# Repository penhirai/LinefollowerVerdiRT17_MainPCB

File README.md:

# LinefollowerVerdiRT17_MainPCB
Micromouse Robotrace Competition

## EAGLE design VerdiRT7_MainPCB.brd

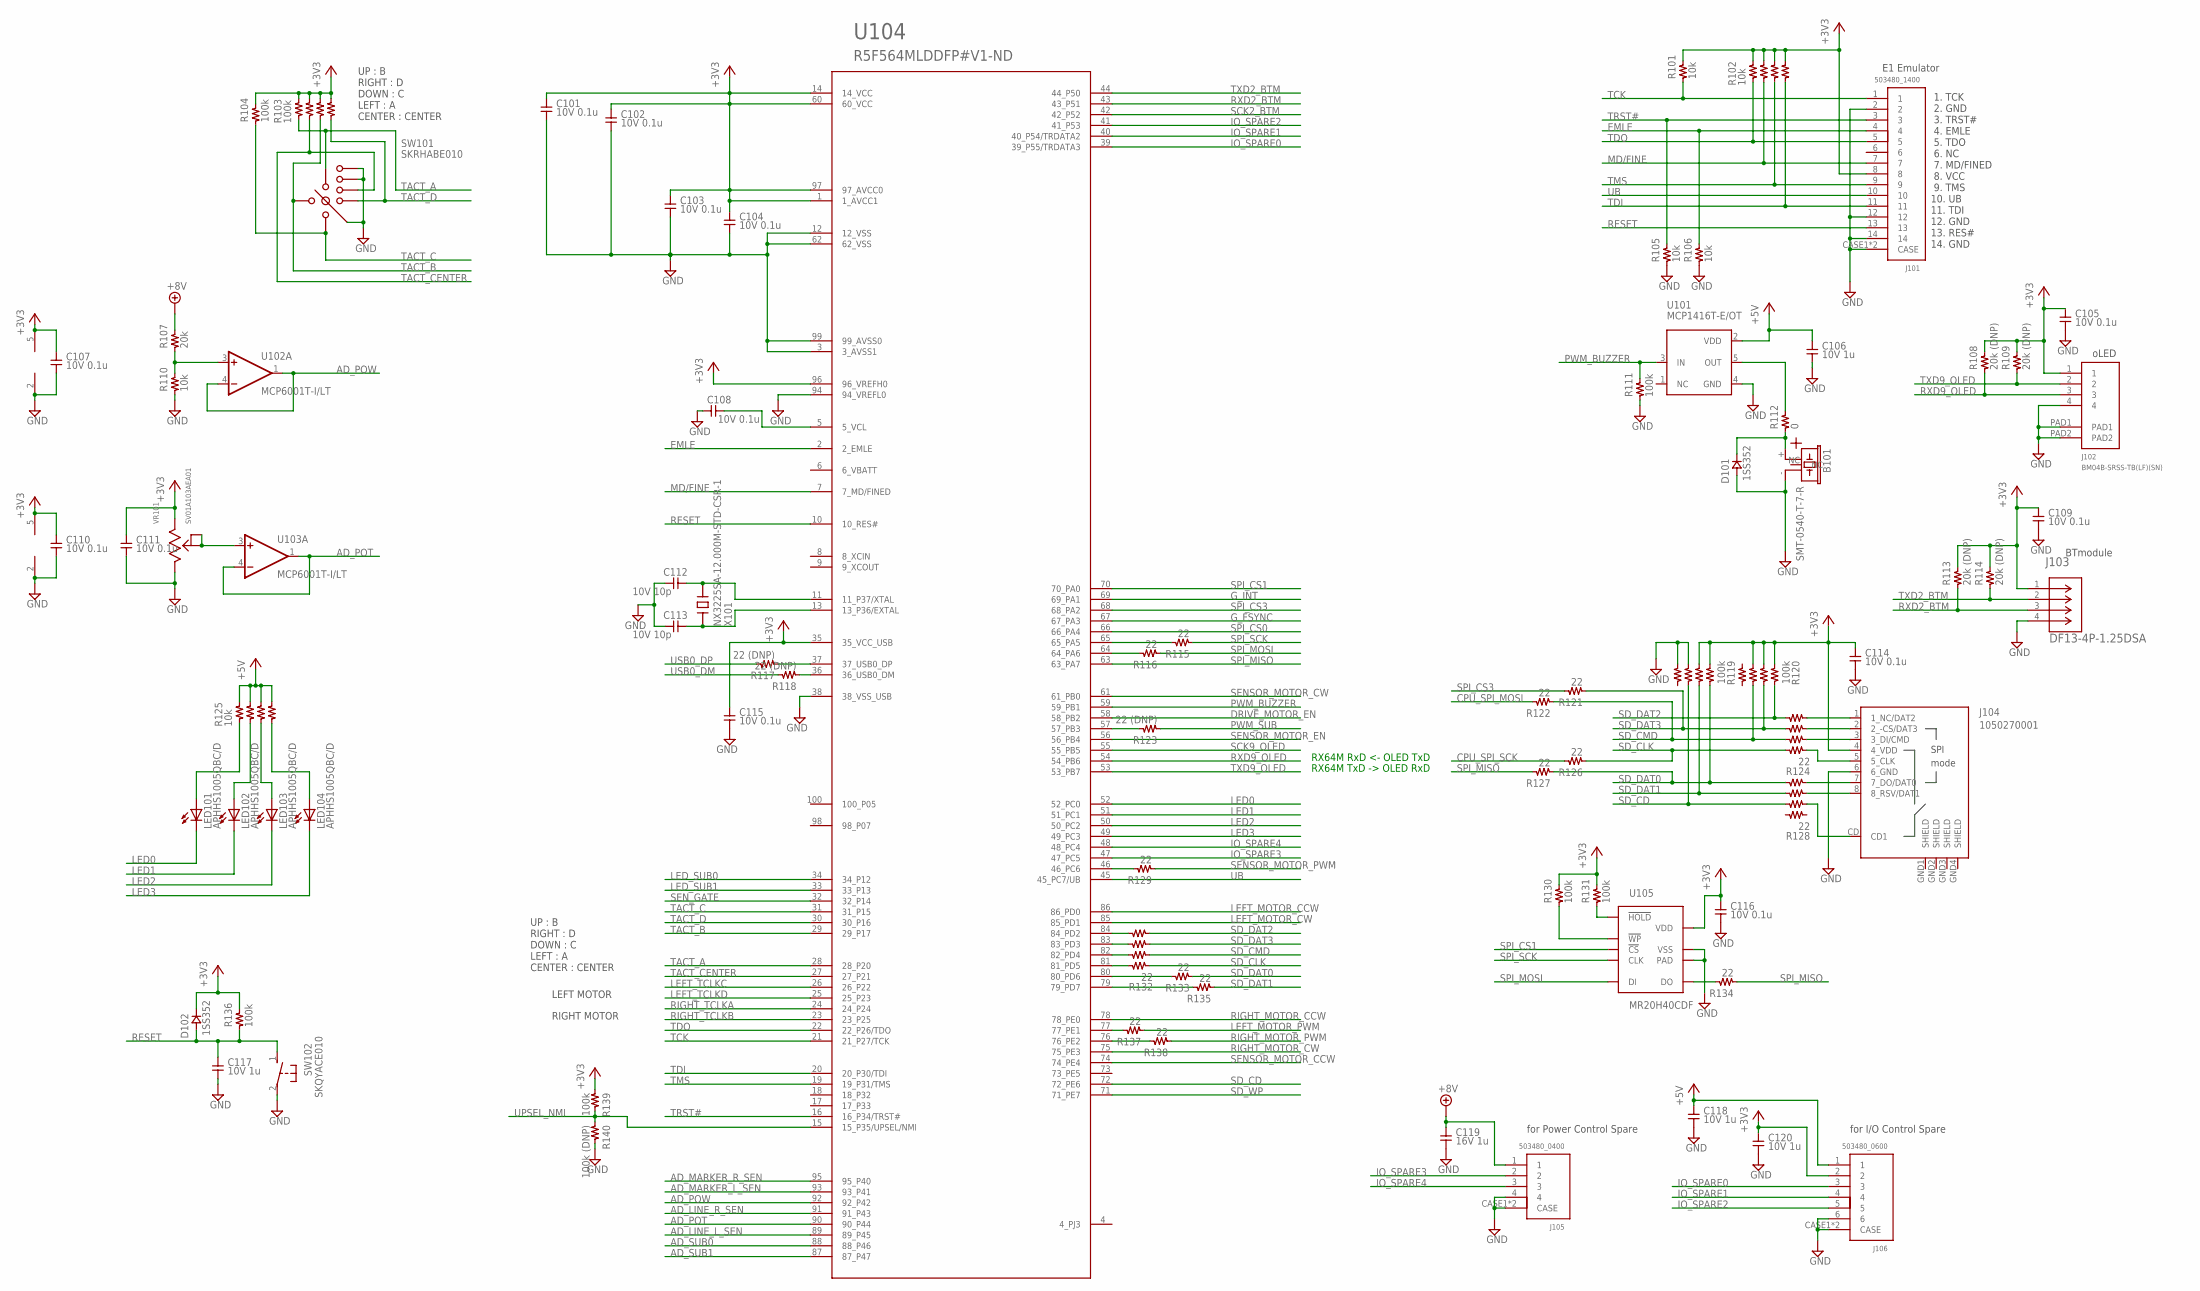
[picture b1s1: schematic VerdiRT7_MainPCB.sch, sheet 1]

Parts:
B101: SMT-0540-T-7-R; SMT-0540-S-R
C101, C102, C103, C104, C105, C107, C108, C109, C110, C111, C114, C115, C116: 10V 0.1u; 1005
C106, C117, C118, C120: 10V 1u; 1005
C112, C113: 10V 10p; 1005
C119: 16V 1u; 1005
D101, D102: 1SS352; 2012
J101: 503480_1400; 1400
J102: BM04B-SRSS-TB(LF)(SN); BM04B-SRSS-TB
J103: DF13-4P-1.25DSA; DF13_4P_TH
J104: 1050270001; MOLEX_105027
J105: 503480_0400; 0400
J106: 503480_0600; 0600
LED101, LED102, LED103, LED104: APHHS1005QBC/D; 1005
R101, R105, R106, R110: 10k; 1005
R102, R125: 10k; 3216_ARRAY
R103, R119, R120: 100k; 3216_ARRAY
R104, R111, R130, R131, R136, R139: 100k; 1005
R107: 20k; 1005
R108, R109, R113, R114: 20k (DNP); 1005
R112: 0; 1005
R115, R116, R121, R122, R126, R127, R129, R133, R134, R135, R137, R138: 22; 1005
R117, R118, R123: 22 (DNP); 1005
R124, R128, R132: 22; 3216_ARRAY
R140: 100k (DNP); 1005
SW101: SKRHABE010; SKRH
SW102: SKQYACE010; SKQYA
U101: MCP1416T-E/OT; SOT23-5
U102, U103: MCP6001T-I/LT; SOT-70-5
U104: R5F564MLDDFP#V1-ND; TQFP100-16X16
U105: MR20H40CDF; 8DFN
VR101: SV01A103AEA01; SV01
X101: NX3225SA-12.000M-STD-CSR-1; 3225

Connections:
+3V3: C101.P$1, C102.P$1, C103.P$1, C104.P$1, C105.P$1, C107.P$1, C109.P$1, C110.P$1, C111.P$1, C114.P$1, C115.P$1, C116.P$1, C120.P$1, D102.K, J101.8, J102.1, J103.1, J104.4 (4_VDD), J106.2, R101.P$2, R102.R1-B, R102.R2-B, R102.R3-B, R102.R4-B, R103.R1-B, R103.R2-B, R103.R3-B, R103.R4-B, R104.P$2, R108.P$2, R109.P$2, R113.P$2, R114.P$2, R119.R1-A, R119.R2-A, R120.R1-A, R120.R2-A, R120.R3-A, R130.P$2, R131.P$2, R136.P$2, R139.P$1, U102.5 (V+), U103.5 (V+), U104.1 (1_AVCC1), U104.14 (14_VCC), U104.35 (35_VCC_USB), U104.60 (60_VCC), U104.96 (96_VREFH0), U104.97 (97_AVCC0), U105.8 (VDD), VR101.2; also elsewhere on the board
+5V: C106.P$1, C118.P$1, J106.1, R125.R1-B, R125.R2-B, R125.R3-B, R125.R4-B, U101.2 (VDD); also elsewhere on the board
+8V: C119.P$1, J105.1, R107.P$2; also elsewhere on the board
AD_LINE_L_SEN: U104.89 (89_P45); also elsewhere on the board
AD_LINE_R_SEN: U104.91 (91_P43); also elsewhere on the board
AD_MARKER_L_SEN: U104.93 (93_P41); also elsewhere on the board
AD_MARKER_R_SEN: U104.95 (95_P40); also elsewhere on the board
AD_POT: U103.1 (OUT), U103.4 (-IN), U104.90 (90_P44)
AD_POW: U102.1 (OUT), U102.4 (-IN), U104.92 (92_P42)
AD_SUB0: U104.88 (88_P46)
AD_SUB1: U104.87 (87_P47)
CPU_SD_DAT0: R133.P$2, U104.80 (80_PD6)
CPU_SPI_MOSI: R116.P$2, R122.P$2, U104.64 (64_PA6)
CPU_SPI_SCK: R115.P$2, R126.P$2, U104.65 (65_PA5)
DRIVE_MOTOR_EN: U104.58 (58_PB2); also elsewhere on the board
EMLE: J101.4, R106.P$2, U104.2 (2_EMLE)
GND: B101.-, C101.P$2, C102.P$2, C103.P$2, C104.P$2, C105.P$2, C106.P$2, C107.P$2, C108.P$2, C109.P$2, C110.P$2, C111.P$2, C112.P$2, C113.P$2, C114.P$2, C115.P$2, C116.P$2, C117.P$2, C118.P$2, C119.P$2, C120.P$2, D101.A, J101.2, J101.12, J101.14, J101.CASE1 (CASE), J101.CASE2 (CASE), J102.4, J102.PAD1, J102.PAD2, J103.4, J104.6 (6_GND), J105.4, J105.CASE1 (CASE), J105.CASE2 (CASE), J106.6, J106.CASE1 (CASE), J106.CASE2 (CASE), R105.P$1, R106.P$1, R110.P$1, R111.P$1, R119.R3-A, R119.R4-A, R140.P$2, SW101.1, SW101.2, SW101.COMMON, SW102.2, U101.4 (GND), U102.2 (V-), U103.2 (V-), U104.3 (3_AVSS1), U104.12 (12_VSS), U104.38 (38_VSS_USB), U104.62 (62_VSS), U104.94 (94_VREFL0), U104.99 (99_AVSS0), U105.4 (VSS), U105.PAD, VR101.1; also elsewhere on the board
G_FSYNC: U104.67 (67_PA3); also elsewhere on the board
G_INT: U104.69 (69_PA1); also elsewhere on the board
IO_SPARE0: J106.3, U104.39 (39_P55/TRDATA3)
IO_SPARE1: J106.4, U104.40 (40_P54/TRDATA2)
IO_SPARE2: J106.5, U104.41 (41_P53)
IO_SPARE3: J105.2, U104.47 (47_PC5)
IO_SPARE4: J105.3, U104.48 (48_PC4)
LED0: LED101.K, U104.52 (52_PC0)
LED1: LED102.K, U104.51 (51_PC1)
LED2: LED103.K, U104.50 (50_PC2)
LED3: LED104.K, U104.49 (49_PC3)
LED_SUB0: U104.34 (34_P12)
LED_SUB1: U104.33 (33_P13)
LEFT_MOTOR_CCW: U104.86 (86_PD0); also elsewhere on the board
LEFT_MOTOR_CW: U104.85 (85_PD1); also elsewhere on the board
LEFT_MOTOR_PWM: R137.P$1; also elsewhere on the board
LEFT_TCLKC: U104.26 (26_P22); also elsewhere on the board
LEFT_TCLKD: U104.25 (25_P23); also elsewhere on the board
MD/FINE: J101.7, R102.R2-A, U104.7 (7_MD/FINED)
unnamed: C108.P$1, U104.5 (5_VCL)
unnamed: C112.P$1, U104.11 (11_P37/XTAL), X101.3
unnamed: R131.P$1, U105.7 (!HOLD)
unnamed: R112.P$2, U101.5 (OUT)
unnamed: B101.+, D101.K, R112.P$1
unnamed: U103.3 (+IN), VR101.3, VR101.4
unnamed: R130.P$1, U105.3 (!WP)
unnamed: C113.P$1, U104.13 (13_P36/EXTAL), X101.1
unnamed: J104.5 (5_CLK), R124.R1-A
unnamed: J104.3 (3_DI/CMD), R124.R2-A
unnamed: J104.2 (2_-CS/DAT3), R124.R3-A
unnamed: R107.P$1, R110.P$2, U102.3 (+IN)
unnamed: J104.1 (1_NC/DAT2), R124.R4-A
unnamed: J104.8 (8_RSV/DAT1), R128.R3-A
unnamed: R134.P$2, U105.2 (DO)
unnamed: J104.7 (7_DO/DAT0), R128.R4-A
unnamed: LED101.A, R125.R1-A
unnamed: LED102.A, R125.R2-A
unnamed: LED103.A, R125.R3-A
unnamed: LED104.A, R125.R4-A
unnamed: J104.CD (CD1), R128.R2-A
unnamed: R132.R4-B, U104.84 (84_PD2)
unnamed: R132.R3-B, U104.83 (83_PD3)
unnamed: R132.R2-B, U104.82 (82_PD4)
unnamed: R132.R1-B, U104.81 (81_PD5)
unnamed: R135.P$2, U104.79 (79_PD7)
unnamed: R123.P$2, U104.57 (57_PB3)
unnamed: R117.P$1, U104.37 (37_USB0_DP)
unnamed: R118.P$1, U104.36 (36_USB0_DM)
PWM_BUZZER: R111.P$2, U101.3 (IN), U104.59 (59_PB1)
PWM_MOT1_MPU: R137.P$2, U104.77 (77_PE1)
PWM_MOT2_MPU: R138.P$2, U104.76 (76_PE2)
PWM_MOT3_MPU: R129.P$2, U104.46 (46_PC6)
PWM_SUB: R123.P$1
RESET: C117.P$1, D102.A, J101.13, R136.P$1, SW102.1, U104.10 (10_RES#)
RIGHT_MOTOR_CCW: U104.78 (78_PE0); also elsewhere on the board
RIGHT_MOTOR_CW: U104.75 (75_PE3); also elsewhere on the board
RIGHT_MOTOR_PWM: R138.P$1; also elsewhere on the board
RIGHT_TCLKA: U104.24 (24_P24); also elsewhere on the board
RIGHT_TCLKB: U104.23 (23_P25); also elsewhere on the board
RXD2_BTM: J103.3, R113.P$1, U104.43 (43_P51)
RXD9_OLED: J102.3, R108.P$1, U104.54 (54_PB6)
SCK2_BTM: U104.42 (42_P52)
SCK9_OLED: U104.55 (55_PB5)
SD_CD: R119.R3-B, R128.R2-B, U104.72 (72_PE6)
SD_CLK: R124.R1-B, R126.P$1, R132.R1-A
SD_CMD: R120.R3-B, R122.P$1, R124.R2-B, R132.R2-A
SD_DAT0: R119.R1-B, R127.P$1, R128.R4-B, R133.P$1
SD_DAT1: R119.R2-B, R128.R3-B, R135.P$1
SD_DAT2: R120.R1-B, R124.R4-B, R132.R4-A
SD_DAT3: R120.R2-B, R121.P$1, R124.R3-B, R132.R3-A
SD_WP: U104.71 (71_PE7)
SENSOR_MOTOR_CCW: U104.74 (74_PE4); also elsewhere on the board
SENSOR_MOTOR_CW: U104.61 (61_PB0); also elsewhere on the board
SENSOR_MOTOR_EN: U104.56 (56_PB4); also elsewhere on the board
SENSOR_MOTOR_PWM: R129.P$1; also elsewhere on the board
SEN_GATE: U104.32 (32_P14); also elsewhere on the board
SPI_CS0: U104.66 (66_PA4); also elsewhere on the board
SPI_CS1: U104.70 (70_PA0), U105.1 (!CS)
SPI_CS3: R121.P$2, U104.68 (68_PA2)
SPI_MISO: R127.P$2, R134.P$1, U104.63 (63_PA7); also elsewhere on the board
SPI_MOSI: R116.P$1, U105.5 (DI); also elsewhere on the board
SPI_SCK: R115.P$1, U105.6 (CLK); also elsewhere on the board
TACT_A: R103.R1-A, SW101.A, U104.28 (28_P20)
TACT_B: R103.R3-A, SW101.B, U104.29 (29_P17)
TACT_C: R104.P$1, SW101.C, U104.31 (31_P15)
TACT_CENTER: R103.R2-A, SW101.CENTER, U104.27 (27_P21)
TACT_D: R103.R4-A, SW101.D, U104.30 (30_P16)
TCK: J101.1, R101.P$1, U104.21 (21_P27/TCK)
TDI: J101.11, R102.R4-A, U104.20 (20_P30/TDI)
TDO: J101.5, R102.R1-A, U104.22 (22_P26/TDO)
TMS: J101.9, R102.R3-A, U104.19 (19_P31/TMS)
TRST#: J101.3, R105.P$2, U104.16 (16_P34/TRST#)
TXD2_BTM: J103.2, R114.P$1, U104.44 (44_P50)
TXD9_OLED: J102.2, R109.P$1, U104.53 (53_PB7)
UB: J101.10, U104.45 (45_PC7/UB)
UPSEL_NMI: R139.P$2, R140.P$1, U104.15 (15_P35/UPSEL/NMI)
USB0_DM: R118.P$2
USB0_DP: R117.P$2

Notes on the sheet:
oLED
E1 Emulator
RX64M TxD -> OLED RxD
RX64M RxD <- OLED TxD
BTmodule
UP : B RIGHT : D DOWN : C LEFT : A CENTER : CENTER
LEFT MOTOR
RIGHT MOTOR
1. TCK 2. GND 3. TRST# 4. EMLE 5. TDO 6. NC 7. MD/FINED 8. VCC 9. TMS 10. UB 11. TDI 12. GND 13. RES# 14. GND
for Power Control Spare
for I/O Control Spare

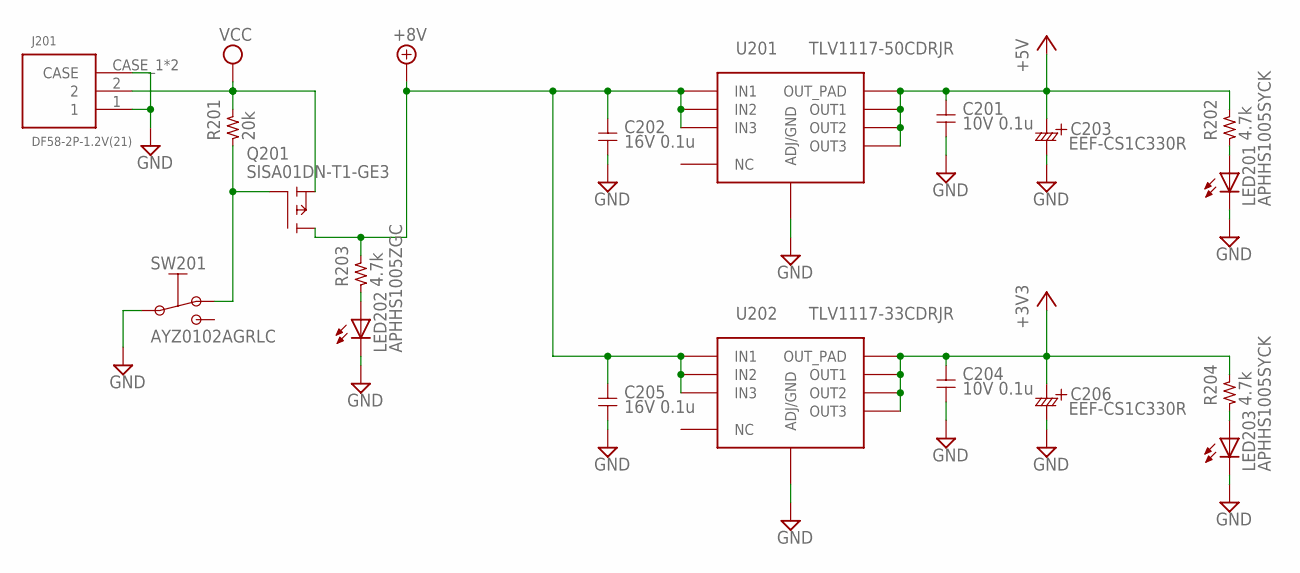
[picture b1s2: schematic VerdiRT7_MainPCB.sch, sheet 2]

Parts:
C201, C204: 10V 0.1u; 1005
C202, C205: 16V 0.1u; 1005
C203, C206: EEF-CS1C330R; EEFC_7343
J201: DF58-2P-1.2V(21); DF58_2P
LED201, LED203: APHHS1005SYCK; 1005
LED202: APHHS1005ZGC; 1005
Q201: SISA01DN-T1-GE3; POWERPAK1212-8
R201: 20k; 1005
R202, R203, R204: 4.7k; 1005
SW201: AYZ0102AGRLC
U201: TLV1117-50CDRJR; WFDFN8
U202: TLV1117-33CDRJR; WFDFN8

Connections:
+3V3: C204.P$1, C206.PLUS, R204.P$2, U202.5 (OUT1), U202.6 (OUT2), U202.7 (OUT3), U202.PAD (OUT_PAD); also elsewhere on the board
+5V: C201.P$1, C203.PLUS, R202.P$2, U201.5 (OUT1), U201.6 (OUT2), U201.7 (OUT3), U201.PAD (OUT_PAD); also elsewhere on the board
+8V: C202.P$1, C205.P$1, Q201.5 (D), Q201.9 (D), R203.P$2, U201.2 (IN1), U201.3 (IN2), U201.4 (IN3), U202.2 (IN1), U202.3 (IN2), U202.4 (IN3); also elsewhere on the board
GND: C201.P$2, C202.P$2, C203.MINUS, C204.P$2, C205.P$2, C206.MINUS, J201.1, J201.CASE_1 (CASE), J201.CASE_2 (CASE), LED201.K, LED202.K, LED203.K, SW201.2, U201.1 (ADJ/GND), U202.1 (ADJ/GND); also elsewhere on the board
unnamed: Q201.4 (G), R201.P$1, SW201.1
unnamed: LED202.A, R203.P$1
unnamed: LED201.A, R202.P$1
unnamed: LED203.A, R204.P$1
VCC: J201.2, Q201.1 (S), R201.P$2

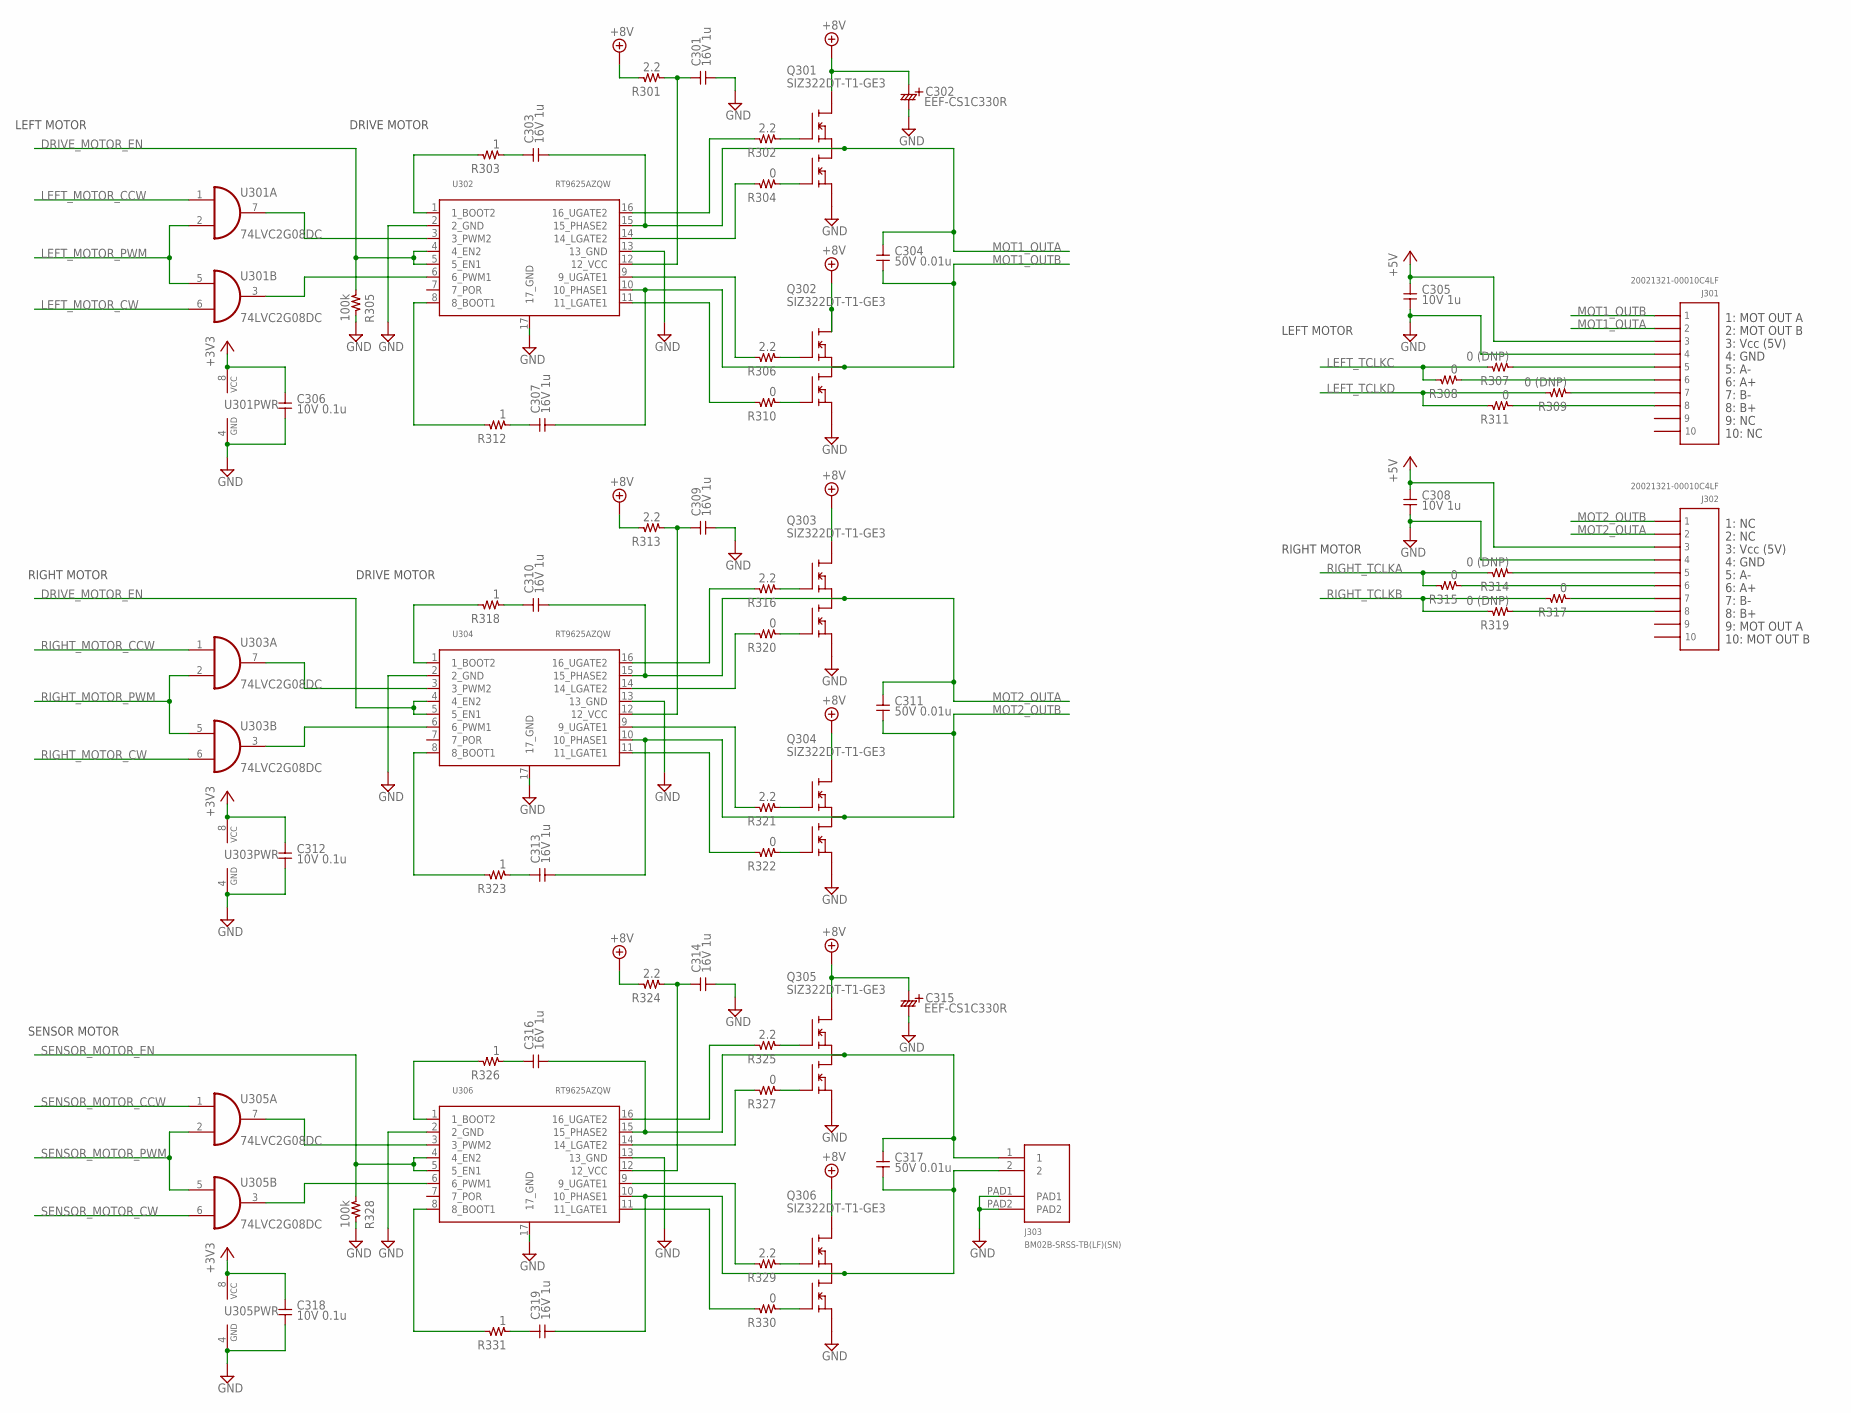
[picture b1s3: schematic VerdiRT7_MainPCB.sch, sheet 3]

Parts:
C301, C303, C307, C309, C310, C313, C314, C316, C319: 16V 1u; 1005
C302, C315: EEF-CS1C330R; EEFC_7343
C304, C311, C317: 50V 0.01u; 1005
C305, C308: 10V 1u; 1005
C306, C312, C318: 10V 0.1u; 1005
J301, J302: 20021321-00010C4LF; MA5-2_SMD_1.27MM_MIN
J303: BM02B-SRSS-TB(LF)(SN); BM02B-SRSS-TB
Q301, Q302, Q303, Q304, Q305, Q306: SIZ322DT-T1-GE3; DFN3X3A
R301, R302, R306, R313, R316, R321, R324, R325, R329: 2.2; 1005
R303, R312, R318, R323, R326, R331: 1; 1005
R304, R308, R310, R311, R315, R317, R320, R322, R327, R330: 0; 1005
R305, R328: 100k; 1005
R307, R309, R314, R319: 0 (DNP); 1005
U301, U303, U305: 74LVC2G08DC; VSSOP8
U302, U304, U306: RT9625AZQW; WQFN16

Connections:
1_A+: J302.6, R315.P$1
1_A-: J302.5, R314.P$1
2_B+: J302.8, R319.P$1
2_B-: J302.7, R317.P$1
3_A+: J301.6, R308.P$1
3_A-: J301.5, R307.P$1
4_B+: J301.8, R311.P$1
4_B-: J301.7, R309.P$1
+3V3: C306.P$1, C312.P$1, C318.P$1, U301.8 (VCC), U303.8 (VCC), U305.8 (VCC); also elsewhere on the board
+5V: C305.P$1, C308.P$1, J301.3, J302.3; also elsewhere on the board
+8V: C302.PLUS, C315.PLUS, Q301.2 (D1), Q301.3 (D1), Q301.4 (D1), Q301.PAD_S (D1), Q302.2 (D1), Q302.3 (D1), Q302.4 (D1), Q302.PAD_S (D1), Q303.2 (D1), Q303.3 (D1), Q303.4 (D1), Q303.PAD_S (D1), Q304.2 (D1), Q304.3 (D1), Q304.4 (D1), Q304.PAD_S (D1), Q305.2 (D1), Q305.3 (D1), Q305.4 (D1), Q305.PAD_S (D1), Q306.2 (D1), Q306.3 (D1), Q306.4 (D1), Q306.PAD_S (D1), R301.P$2, R313.P$2, R324.P$2; also elsewhere on the board
DRIVE_MOTOR_EN: R305.P$1, U302.4 (4_EN2), U302.5 (5_EN1), U304.4 (4_EN2), U304.5 (5_EN1); also elsewhere on the board
GND: C301.P$2, C302.MINUS, C305.P$2, C306.P$2, C308.P$2, C309.P$2, C312.P$2, C314.P$2, C315.MINUS, C318.P$2, J301.4, J302.4, J303.PAD1, J303.PAD2, Q301.5 (S2), Q301.6 (S2), Q301.7 (S2), Q302.5 (S2), Q302.6 (S2), Q302.7 (S2), Q303.5 (S2), Q303.6 (S2), Q303.7 (S2), Q304.5 (S2), Q304.6 (S2), Q304.7 (S2), Q305.5 (S2), Q305.6 (S2), Q305.7 (S2), Q306.5 (S2), Q306.6 (S2), Q306.7 (S2), R305.P$2, R328.P$2, U301.4 (GND), U302.2 (2_GND), U302.13 (13_GND), U302.17 (17_GND), U303.4 (GND), U304.2 (2_GND), U304.13 (13_GND), U304.17 (17_GND), U305.4 (GND), U306.2 (2_GND), U306.13 (13_GND), U306.17 (17_GND); also elsewhere on the board
LEFT_MOTOR_CCW: U301.1 (I0); also elsewhere on the board
LEFT_MOTOR_CW: U301.6 (I1); also elsewhere on the board
LEFT_MOTOR_PWM: U301.2 (I1), U301.5 (I0); also elsewhere on the board
LEFT_TCLKC: R307.P$2, R308.P$2; also elsewhere on the board
LEFT_TCLKD: R309.P$2, R311.P$2; also elsewhere on the board
MOT1_OUTA: C303.P$2, C304.P$1, J301.2, Q301.PAD_L (S1D2), U302.15 (15_PHASE2)
MOT1_OUTB: C304.P$2, C307.P$2, J301.1, Q302.PAD_L (S1D2), U302.10 (10_PHASE1)
MOT2_OUTA: C310.P$2, C311.P$1, J302.2, Q303.PAD_L (S1D2), U304.15 (15_PHASE2)
MOT2_OUTB: C311.P$2, C313.P$2, J302.1, Q304.PAD_L (S1D2), U304.10 (10_PHASE1)
unnamed: C317.P$2, C319.P$2, J303.2, Q306.PAD_L (S1D2), U306.10 (10_PHASE1)
unnamed: Q306.1 (G1), R329.P$1
unnamed: Q306.8 (G2), R330.P$1
unnamed: R318.P$2, U304.1 (1_BOOT2)
unnamed: C310.P$1, R318.P$1
unnamed: R323.P$2, U304.8 (8_BOOT1)
unnamed: C313.P$1, R323.P$1
unnamed: C309.P$1, R313.P$1, U304.12 (12_VCC)
unnamed: U303.7 (O), U304.3 (3_PWM2)
unnamed: U303.3 (O), U304.6 (6_PWM1)
unnamed: R322.P$2, U304.11 (11_LGATE1)
unnamed: R321.P$2, U304.9 (9_UGATE1)
unnamed: R320.P$2, U304.14 (14_LGATE2)
unnamed: Q303.8 (G2), R320.P$1
unnamed: R316.P$2, U304.16 (16_UGATE2)
unnamed: Q303.1 (G1), R316.P$1
unnamed: Q304.1 (G1), R321.P$1
unnamed: Q304.8 (G2), R322.P$1
unnamed: R303.P$2, U302.1 (1_BOOT2)
unnamed: C303.P$1, R303.P$1
unnamed: R312.P$2, U302.8 (8_BOOT1)
unnamed: C307.P$1, R312.P$1
unnamed: C301.P$1, R301.P$1, U302.12 (12_VCC)
unnamed: U301.7 (O), U302.3 (3_PWM2)
unnamed: U301.3 (O), U302.6 (6_PWM1)
unnamed: R310.P$2, U302.11 (11_LGATE1)
unnamed: R306.P$2, U302.9 (9_UGATE1)
unnamed: R304.P$2, U302.14 (14_LGATE2)
unnamed: Q301.8 (G2), R304.P$1
unnamed: R326.P$2, U306.1 (1_BOOT2)
unnamed: C316.P$1, R326.P$1
unnamed: C316.P$2, C317.P$1, J303.1, Q305.PAD_L (S1D2), U306.15 (15_PHASE2)
unnamed: R331.P$2, U306.8 (8_BOOT1)
unnamed: C319.P$1, R331.P$1
unnamed: R302.P$2, U302.16 (16_UGATE2)
unnamed: C314.P$1, R324.P$1, U306.12 (12_VCC)
unnamed: U305.7 (O), U306.3 (3_PWM2)
unnamed: U305.3 (O), U306.6 (6_PWM1)
unnamed: R330.P$2, U306.11 (11_LGATE1)
unnamed: Q301.1 (G1), R302.P$1
unnamed: R327.P$2, U306.14 (14_LGATE2)
unnamed: R329.P$2, U306.9 (9_UGATE1)
unnamed: Q305.8 (G2), R327.P$1
unnamed: R325.P$2, U306.16 (16_UGATE2)
unnamed: Q305.1 (G1), R325.P$1
unnamed: Q302.1 (G1), R306.P$1
unnamed: Q302.8 (G2), R310.P$1
RIGHT_MOTOR_CCW: U303.1 (I0); also elsewhere on the board
RIGHT_MOTOR_CW: U303.6 (I1); also elsewhere on the board
RIGHT_MOTOR_PWM: U303.2 (I1), U303.5 (I0); also elsewhere on the board
RIGHT_TCLKA: R314.P$2, R315.P$2; also elsewhere on the board
RIGHT_TCLKB: R317.P$2, R319.P$2; also elsewhere on the board
SENSOR_MOTOR_CCW: U305.1 (I0); also elsewhere on the board
SENSOR_MOTOR_CW: U305.6 (I1); also elsewhere on the board
SENSOR_MOTOR_EN: R328.P$1, U306.4 (4_EN2), U306.5 (5_EN1); also elsewhere on the board
SENSOR_MOTOR_PWM: U305.2 (I1), U305.5 (I0); also elsewhere on the board

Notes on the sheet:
SENSOR MOTOR
DRIVE MOTOR
3: Vcc (5V)
4: GND
5: A-
6: A+
7: B-
8: B+
2: MOT OUT B
1: MOT OUT A
9: NC
10: NC
2: NC
1: NC
9: MOT OUT A
10: MOT OUT B
RIGHT MOTOR
LEFT MOTOR

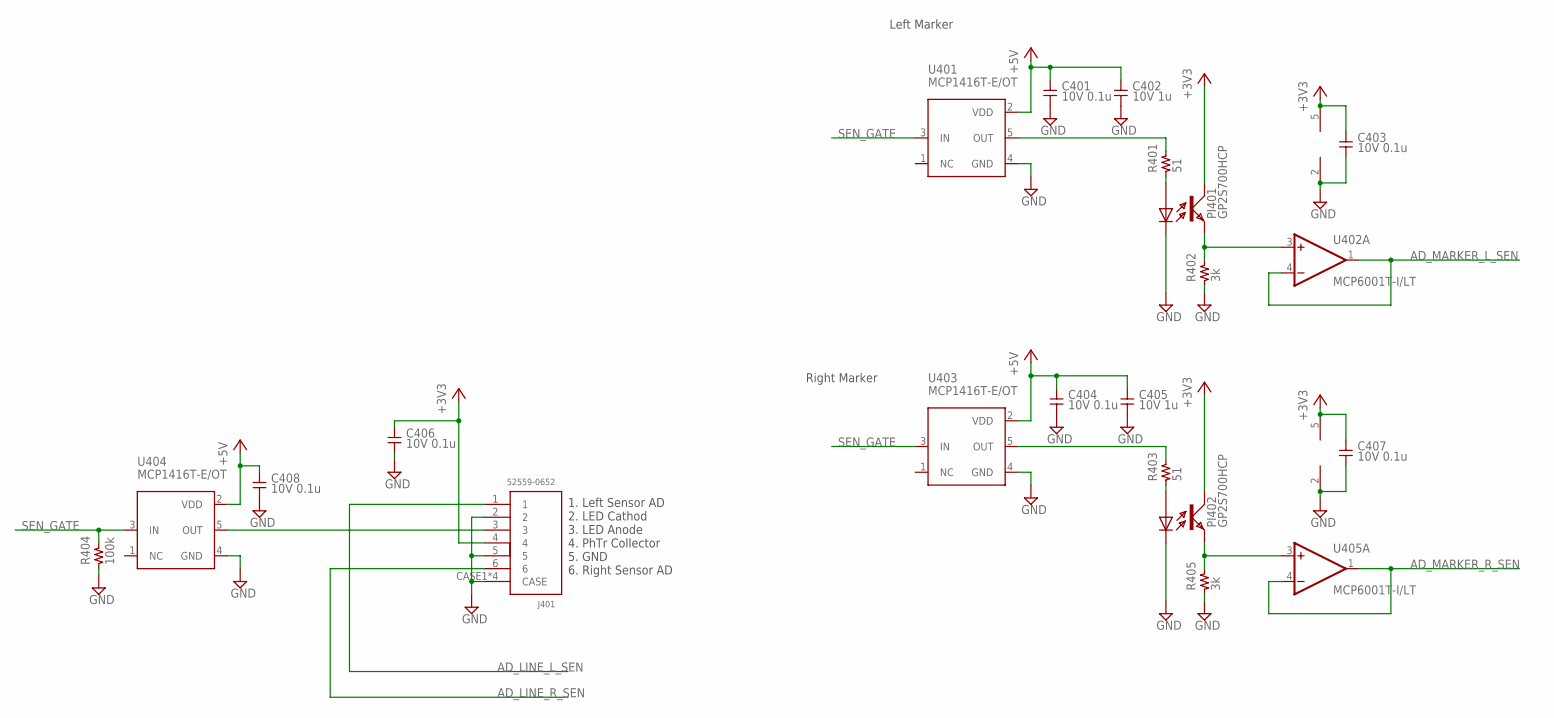
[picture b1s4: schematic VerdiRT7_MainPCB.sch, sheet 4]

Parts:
C401, C403, C404, C406, C407, C408: 10V 0.1u; 1005
C402, C405: 10V 1u; 1005
J401: 52559-0652; 0652
PI401, PI402: GP2S700HCP; GP2S700
R401, R403: 51; 1608
R402, R405: 3k; 1005
R404: 100k; 1005
U401, U403, U404: MCP1416T-E/OT; SOT23-5
U402, U405: MCP6001T-I/LT; SOT-70-5

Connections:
+3V3: C403.P$1, C406.P$1, C407.P$1, J401.4, PI401.COLLECTOR, PI402.COLLECTOR, U402.5 (V+), U405.5 (V+); also elsewhere on the board
+5V: C401.P$1, C402.P$1, C404.P$1, C405.P$1, C408.P$1, U401.2 (VDD), U403.2 (VDD), U404.2 (VDD); also elsewhere on the board
AD_LINE_L_SEN: J401.1; also elsewhere on the board
AD_LINE_R_SEN: J401.6; also elsewhere on the board
AD_MARKER_L_SEN: U402.1 (OUT), U402.4 (-IN); also elsewhere on the board
AD_MARKER_R_SEN: U405.1 (OUT), U405.4 (-IN); also elsewhere on the board
GND: C401.P$2, C402.P$2, C403.P$2, C404.P$2, C405.P$2, C406.P$2, C407.P$2, C408.P$2, J401.2, J401.5, J401.CASE1 (CASE), J401.CASE2 (CASE), J401.CASE3 (CASE), J401.CASE4 (CASE), PI401.CATHODE, PI402.CATHODE, R402.P$1, R404.P$1, R405.P$1, U401.4 (GND), U402.2 (V-), U403.4 (GND), U404.4 (GND), U405.2 (V-); also elsewhere on the board
unnamed: J401.3, U404.5 (OUT)
unnamed: R401.P$2, U401.5 (OUT)
unnamed: PI401.ANODE, R401.P$1
unnamed: PI401.EMITTER, R402.P$2, U402.3 (+IN)
unnamed: R403.P$2, U403.5 (OUT)
unnamed: PI402.ANODE, R403.P$1
unnamed: PI402.EMITTER, R405.P$2, U405.3 (+IN)
SEN_GATE: R404.P$2, U401.3 (IN), U403.3 (IN), U404.3 (IN); also elsewhere on the board

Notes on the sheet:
Left Marker
Right Marker
1. Left Sensor AD 2. LED Cathod 3. LED Anode 4. PhTr Collector 5. GND 6. Right Sensor AD

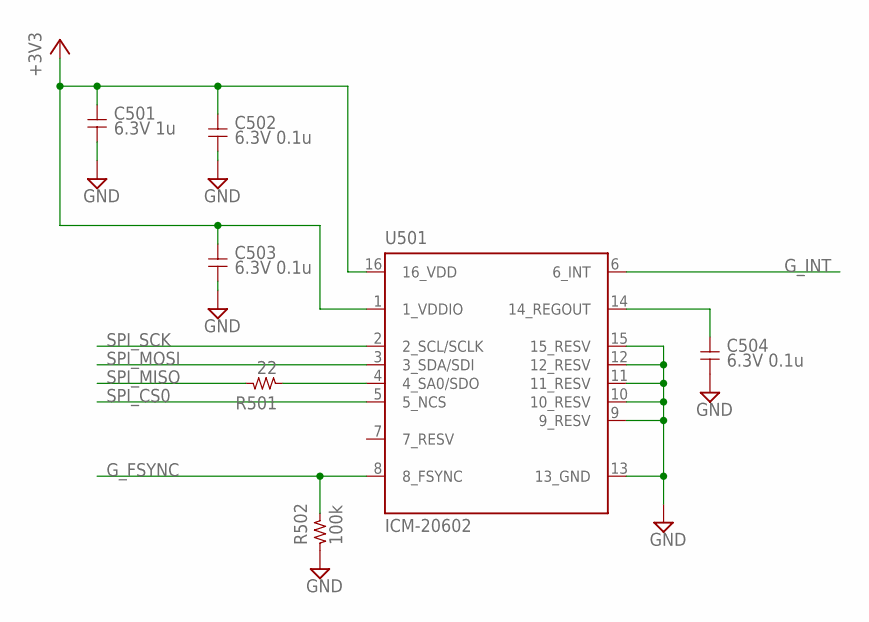
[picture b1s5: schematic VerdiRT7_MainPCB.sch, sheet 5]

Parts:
C501: 6.3V 1u; 1005
C502, C503, C504: 6.3V 0.1u; 1005
R501: 22; 1005
R502: 100k; 1005
U501: ICM-20602; LGA16_3X3MM

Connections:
7_RESV: U501.7 (7_RESV)
+3V3: C501.P$1, C502.P$1, C503.P$1, U501.1 (1_VDDIO), U501.16 (16_VDD); also elsewhere on the board
GND: C501.P$2, C502.P$2, C503.P$2, C504.P$2, R502.P$1, U501.9 (9_RESV), U501.10 (10_RESV), U501.11 (11_RESV), U501.12 (12_RESV), U501.13 (13_GND), U501.15 (15_RESV); also elsewhere on the board
G_FSYNC: R502.P$2, U501.8 (8_FSYNC); also elsewhere on the board
G_INT: U501.6 (6_INT); also elsewhere on the board
unnamed: C504.P$1, U501.14 (14_REGOUT)
unnamed: R501.P$1, U501.4 (4_SA0/SDO)
SPI_CS0: U501.5 (5_NCS); also elsewhere on the board
SPI_MISO: R501.P$2; also elsewhere on the board
SPI_MOSI: U501.3 (3_SDA/SDI); also elsewhere on the board
SPI_SCK: U501.2 (2_SCL/SCLK); also elsewhere on the board

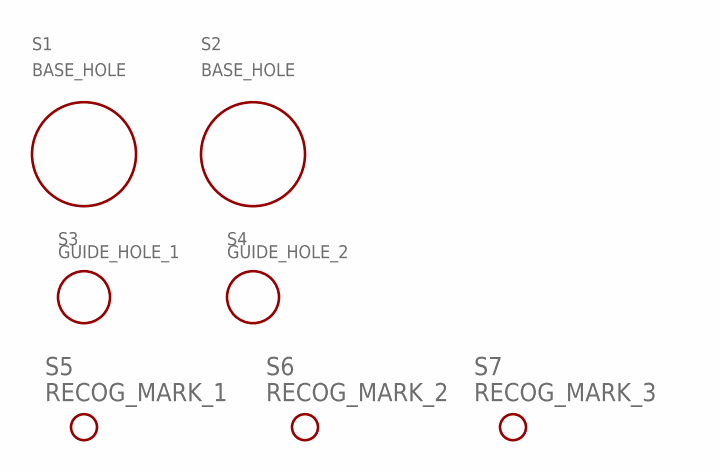
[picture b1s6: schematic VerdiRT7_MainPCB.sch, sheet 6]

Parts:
S1, S2: BASE_HOLE
S3: GUIDE_HOLE_1; GUIDE_HOLE
S4: GUIDE_HOLE_2; GUIDE_HOLE
S5: RECOG_MARK_1; RECOG_MARK
S6: RECOG_MARK_2; RECOG_MARK
S7: RECOG_MARK_3; RECOG_MARK

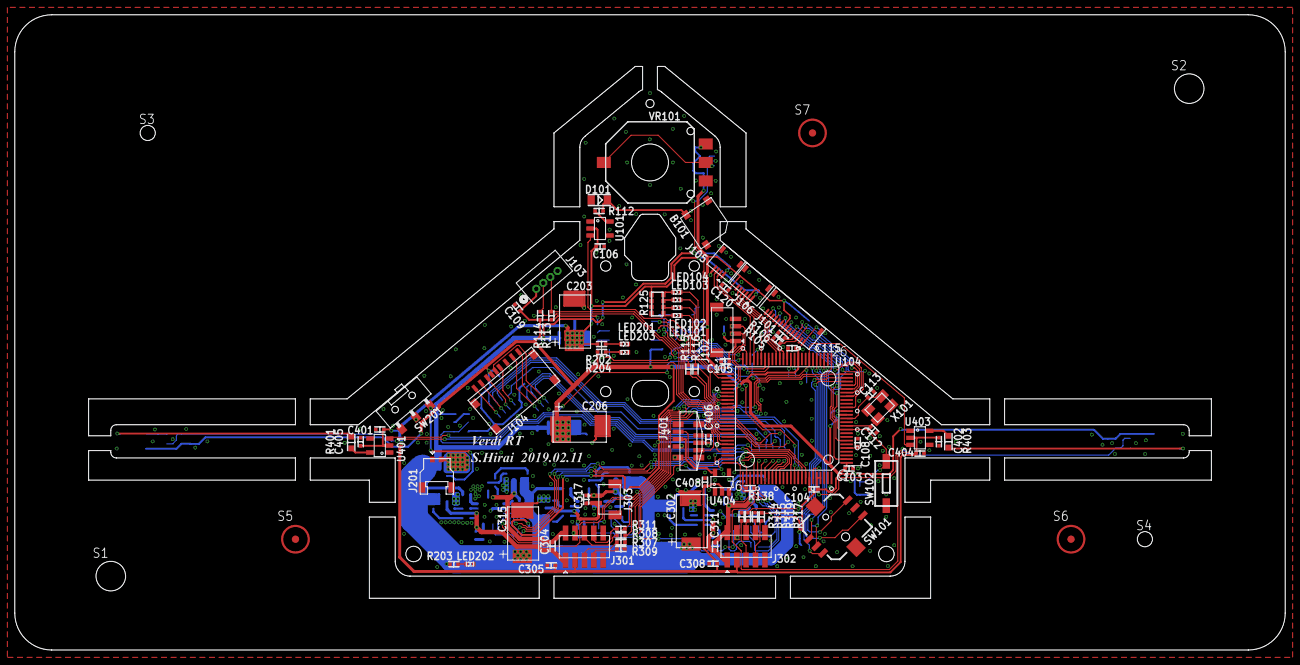
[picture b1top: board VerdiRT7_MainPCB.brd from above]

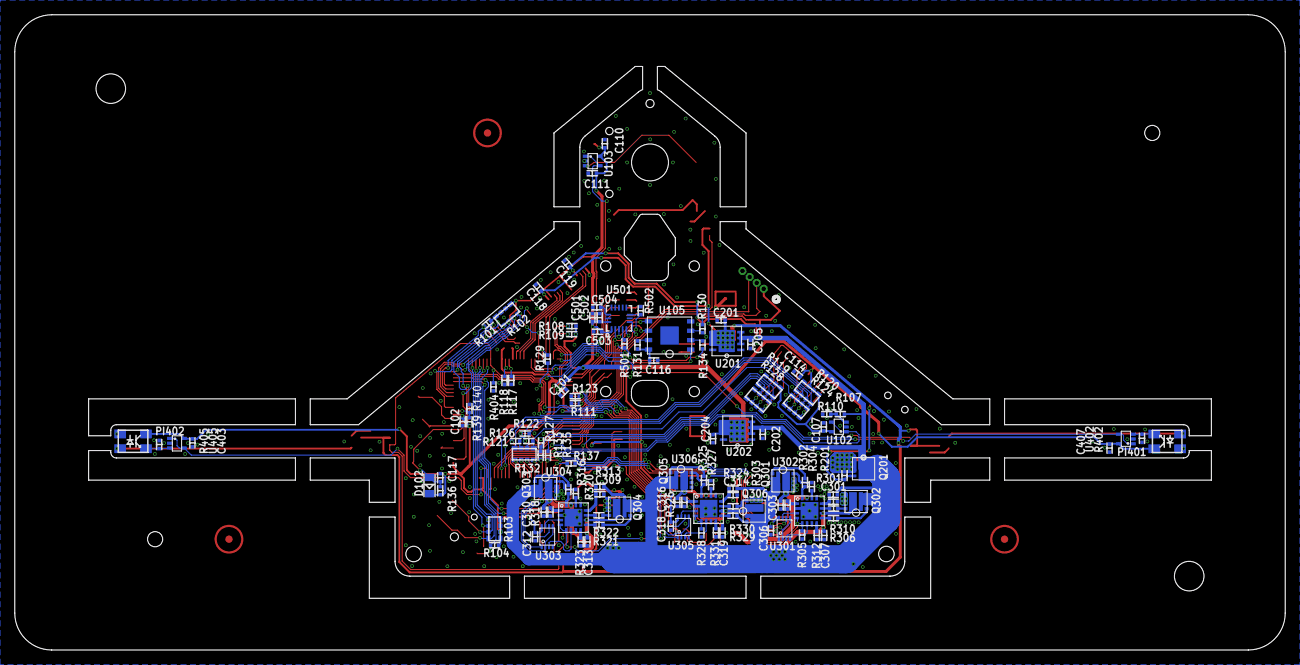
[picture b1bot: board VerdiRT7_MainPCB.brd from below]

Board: 2 copper layers, 172.0 x 86.0 mm, 200 parts (116 on the bottom side), 178 nets.

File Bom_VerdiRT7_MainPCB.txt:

Qty	Value	Device	Package	Parts	Description	CAPACITANCE	FORCE	HEIGHT	MOUNT	REMARK	TEMP	VOLTAGE
11	0	R1005	1005	"R112, R304, R308, R310, R311, R315, R317, R320, R322, R327, R330"				0.35				
4	0 (DNP)	R1005	1005	"R307, R309, R314, R319"				0.35				
6	1	R1005	1005	"R303, R312, R318, R323, R326, R331"				0.35				
3	100k	3216_ARRAY	3216_ARRAY	"R103, R119, R120"				0.5				
10	100k	R1005	1005	"R104, R111, R130, R131, R136, R139, R305, R328, R404, R502"				0.35				
1	100k (DNP)	R1005	1005	R140				0.35				
1	1050270001	1050270001	MOLEX_105027	J104				1.7				
24	10V 0.1u	1005	1005	"C101, C102, C103, C104, C105, C107, C108, C109, C110, C111, C114, C115, C116, C201, C204, C306, C312, C318, C401, C403, C404, C406, C407, C408"				0.5				
2	10V 10p	1005	1005	"C112, C113"				0.5				
8	10V 1u	1005	1005	"C106, C117, C118, C120, C305, C308, C402, C405"				0.5				
2	10k	3216_ARRAY	3216_ARRAY	"R102, R125"				0.5				
4	10k	R1005	1005	"R101, R105, R106, R110"				0.35				
2	16V 0.1u	1005	1005	"C202, C205"				0.5				
10	16V 1u	1005	1005	"C119, C301, C303, C307, C309, C310, C313, C314, C316, C319"				0.5				
2	1SS352	1SS352	2012	"D101, D102"	switching diode			0.9				
9	2.2	R1005	1005	"R301, R302, R306, R313, R316, R321, R324, R325, R329"				0.35				
2	20021321-00010C4LF	20021321-00010C4LF	MA5-2_SMD_1.27MM_MIN	"J301, J302"				4.5				
2	20k	R1005	1005	"R107, R201"				0.35				
4	20k (DNP)	R1005	1005	"R108, R109, R113, R114"				0.35				
3	22	3216_ARRAY	3216_ARRAY	"R124, R128, R132"				0.5				
13	22	R1005	1005	"R115, R116, R121, R122, R126, R127, R129, R133, R134, R135, R137, R138, R501"				0.35				
3	22 (DNP)	R1005	1005	"R117, R118, R123"				0.35				
2	3k	R1005	1005	"R402, R405"				0.35				
3	4.7k	R1005	1005	"R202, R203, R204"				0.35				
1	503480_0400	503480_0400	400	J105				1				
1	503480_0600	503480_0600	600	J106								
1	503480_1400	503480_1400	1400	J101								
3	50V 0.01u	1005	1005	"C304, C311, C317"				0.5				
2	51	R1608	1608	"R401, R403"				0.45				
1	52559-0652	52559-0652	652	J401								
3	6.3V 0.1u	1005	1005	"C502, C503, C504"				0.5				
1	6.3V 1u	1005	1005	C501				0.5				
3	74LVC2G08DC	74LVC2G08DC	VSSOP8	"U301, U303, U305"								
4	APHHS1005QBC/D	LED1005	1005	"LED101, LED102, LED103, LED104"				0.5				
2	APHHS1005SYCK	LED1005	1005	"LED201, LED203"				0.5				
1	APHHS1005ZGC	LED1005	1005	LED202				0.5				
1	AYZ0102AGRLC	AYZ0102AGRLC	AYZ0102AGRLC	SW201				1.5				
2	BASE_HOLE	BASE_HOLE	BASE_HOLE	"S1, S2"				0.1				
1	BM02B-SRSS-TB(LF)(SN)	BM02B-SRSS-TB(LF)(SN)	BM02B-SRSS-TB	J303				6.3				
1	BM04B-SRSS-TB(LF)(SN)	BM04B-SRSS-TB(LF)(SN)	BM04B-SRSS-TB	J102				6.3	top			
1	DF13-4P-1.25DSA	DF13-4P-1.25DSA	DF13_4P_TH	J103								
1	DF58-2P-1.2V(21)	DF58-2P-1.2V(21)	DF58_2P	J201								
4	EEF-CS1C330R	EEF-CS1C330R	EEFC_7343	"C203, C206, C302, C315"		33uF		1.2				16V
2	GP2S700HCP	GP2S700HCP	GP2S700	"PI401, PI402"				2				
1	GUIDE_HOLE_1	GUIDE_HOLE_1	GUIDE_HOLE	S3				0.1				
1	GUIDE_HOLE_2	GUIDE_HOLE_2	GUIDE_HOLE	S4				0.1				
1	ICM-20602	ICM-20602	LGA16_3X3MM	U501				0.8				
4	MCP1416T-E/OT	MCP1416T-E/OT	SOT23-5	"U101, U401, U403, U404"				1.45				
4	MCP6001T-I/LT	MCP6001T-I/LT	SOT-70-5	"U102, U103, U402, U405"				1.1			-40 ~ 85 degC	
1	MR20H40CDF	MR20H40CDF	8DFN	U105				0.8				
1	NX3225SA-12.000M-STD-CSR-1	NX3225SA-12.000M-STD-CSR-1	3225	X101				0.7				
1	R5F564MLDDFP#V1-ND	R5F564MLDDFP#V1-ND	TQFP100-16X16	U104				2.1				
1	RECOG_MARK_1	RECOG_MARK_1	RECOG_MARK	S5				0.1				
1	RECOG_MARK_2	RECOG_MARK_2	RECOG_MARK	S6				0.1				
1	RECOG_MARK_3	RECOG_MARK_3	RECOG_MARK	S7				0.1				
3	RT9625AZQW	RT9625AZQW	WQFN16	"U302, U304, U306"				0.8				
1	SISA01DN-T1-GE3	SISA01DN-T1-GE3	POWERPAK1212-8	Q201								
6	SIZ322DT-T1-GE3	SIZ322DT-T1-GE3	DFN3X3A	"Q301, Q302, Q303, Q304, Q305, Q306"								
1	SKQYACE010	SKQYACE010	SKQYA	SW102			0.98N	2.5				
1	SKRHABE010	SKRHABE010	SKRH	SW101				5				
1	SMT-0540-T-7-R	SMT-0540-T-7-R	SMT-0540-S-R	B101				2.1		top hole		
1	SV01A103AEA01	SV01A103AEA01	SV01	VR101				2.1				
1	TLV1117-33CDRJR	TLV1117-33CDRJR	WFDFN8	U202				0.75				
1	TLV1117-50CDRJR	TLV1117-50CDRJR	WFDFN8	U201				0.75

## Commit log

2018-07-17 added: Eagle Project and Logo, Gerber Data
2018-08-25 updated: AD0 モジュール使用によるピンアサイン変更 P05, P07 を使用しない
2018-09-30 updated: schematic にコメント挿入
2018-10-01 updated: Bluetooth モジュールの電源を+5V -> +3.3V に変更
2019-01-09 updated: コネクタ変更，ディスコンFET 交換
2019-01-09 updated: schema, board のPDF を追加
2019-01-26 updated: DRC 終了
2019-01-26 updated: DRC 後のPDF 更新
2019-02-10 updated: リナンバー完了，BOM 完了
2019-02-10 updated: ファイル構成変更
2019-02-10 updated: PDF 更新
2019-02-10 updated: BOM 追加
2019-02-17 updated: 捨て基板や認識マークを追加．発注データ作成
